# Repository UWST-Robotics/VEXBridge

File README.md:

> ⚠️ **WARNING:** Hey, VEXBridge is still a WIP project. If you run into any bugs or issues, don\'t hesitate to report
> them in the [issues tab](https://github.com/UWST-Robotics/VEXBridge/issues).

<h1 align="center">
VEXBridge
</h1>

<p align="center">
In order to test autonomous routines on mobile robotic systems, receiving feedback during runtime is extremely important. VEXBridge is an app designed to be installed on an SBC such as a Raspberry Pi to relay and present debug data from a serial port (such as a VEX V5 brain) to a developer over Wi-Fi.
</p>

## Features

- 📡 Wireless event log and data communication
- 🗂️ Receive and transmit any data structure
- 🗺️ Display field map for odometry and path planning
- 📈 Graph values over time for easy PID tuning
- ⚠️ Display warnings/errors for both hardware and software diagnostics

## Building

1. Install [Node.js](https://nodejs.org/en) w/ Yarn
2. Install dependencies

```
yarn i
```

3. Run development server

```
yarn run dev
```

## Installing

TODO

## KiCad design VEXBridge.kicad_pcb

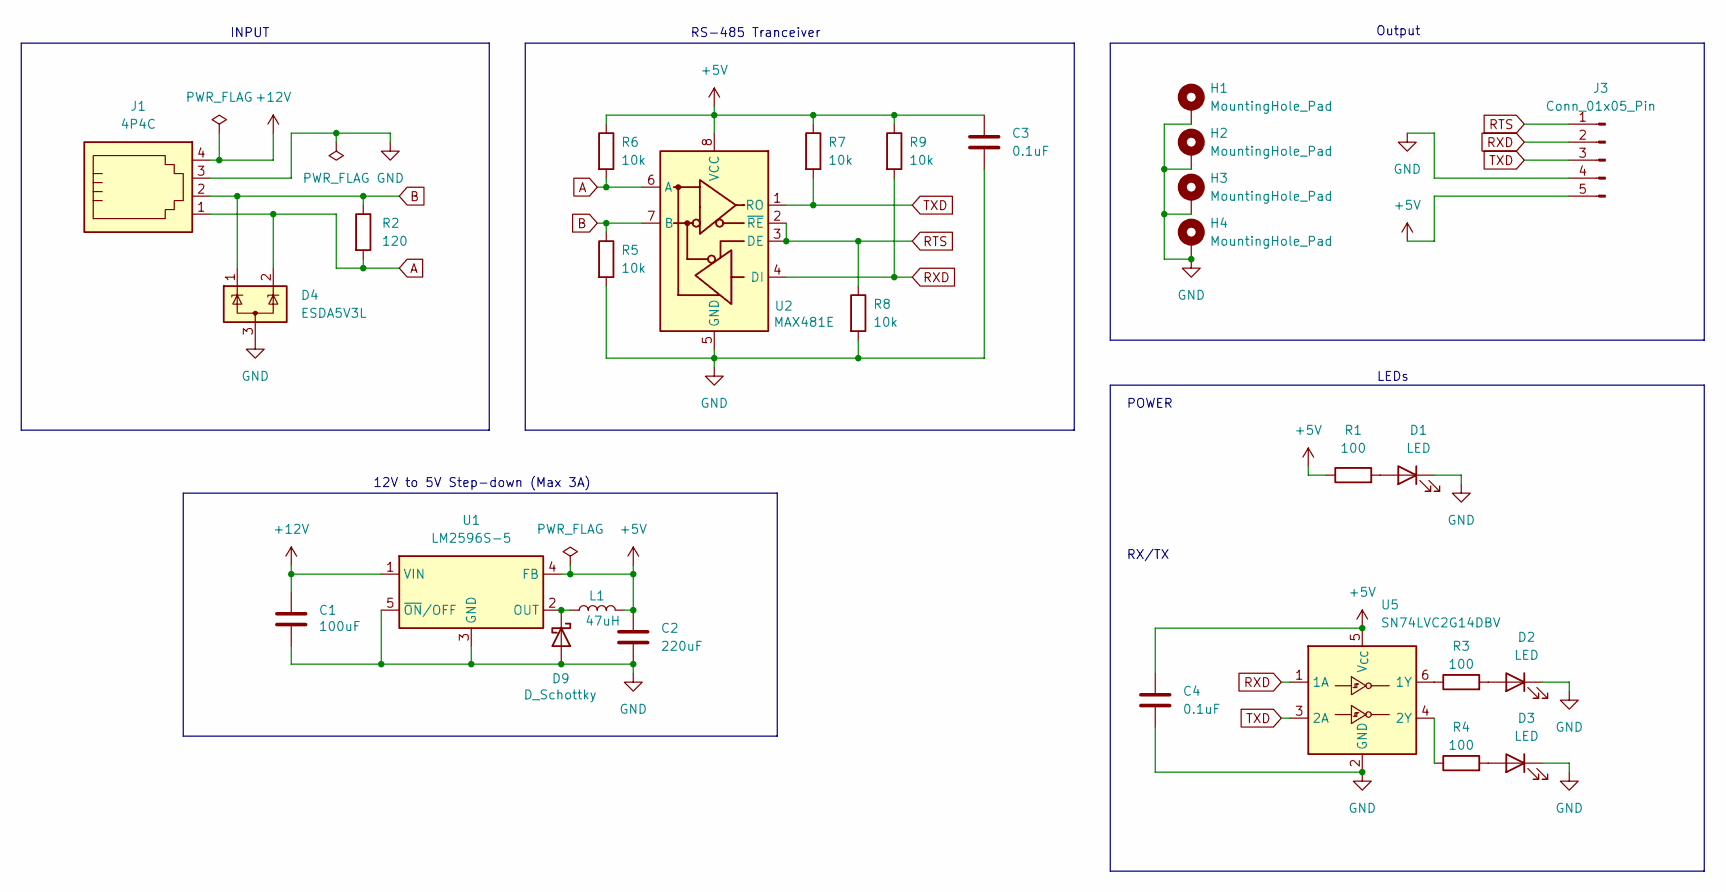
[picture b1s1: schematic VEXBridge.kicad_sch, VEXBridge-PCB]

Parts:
C1: 100uF; CP_Elec_6.3x7.7
C2: 220uF; CP_Elec_6.3x7.7
C3, C4: 0.1uF; C_0402_1005Metric
D1, D2, D3: LED; LED_0603_1608Metric
D4: ESDA5V3L; SOT-23-3
D9: D_Schottky; D_SMA
H1, H2, H3, H4: MountingHole_Pad; MountingHole_2.7mm_M2.5_Pad
J1: 4P4C; RJ9_Evercom_5301-440xxx_Horizontal
J3: Conn_01x05_Pin; PinHeader_1x05_P2.54mm_Vertical
L1: 47uH; L_Coilcraft_LPS4018
R1, R3, R4: 100; R_0805_2012Metric
R2: 120; R_1206_3216Metric
R5, R6, R7, R8, R9: 10k; R_0805_2012Metric
U1: LM2596S-5; TO-263-5_TabPin3
U2: MAX481E; SOIC-8_3.9x4.9mm_P1.27mm
U5: SN74LVC2G14DBV; SOT-23-6

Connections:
+5V: C2.1, C3.1, C4.1, J3.5, L1.2, R1.1, R6.1, R7.1, R9.1, U1.4 (FB), U2.8 (VCC), U5.5 (V_{CC})
+12V: C1.1, J1.4, U1.1 (VIN)
A: D4.2 (K), J1.1, R2.2, R6.2, U2.6 (A)
B: D4.1 (K), J1.2, R2.1, R5.1, U2.7 (B)
GND: C1.2, C2.2, C3.2, C4.2, D1.1 (K), D2.1 (K), D3.1 (K), D4.3 (A), D9.2 (A), H1.1, H2.1, H3.1, H4.1, J1.3, J3.4, R5.2, R8.2, U1.3 (GND), U1.5 (~ON/OFF), U2.5 (GND), U5.2 (GND)
unnamed: D1.2 (A), R1.2
unnamed: D2.2 (A), R3.2
unnamed: D3.2 (A), R4.2
unnamed: D9.1 (K), L1.1, U1.2 (OUT)
unnamed: R3.1, U5.6 (1Y)
unnamed: R4.1, U5.4 (2Y)
RTS: J3.1, R8.1, U2.2 (~RE), U2.3 (DE)
RXD: J3.2, R9.2, U2.4 (DI), U5.1 (1A)
TXD: J3.3, R7.2, U2.1 (RO), U5.3 (2A)

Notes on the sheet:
INPUT
LEDs
RX/TX
POWER
Output
12V to 5V Step-down (Max 3A)
RS-485 Tranceiver

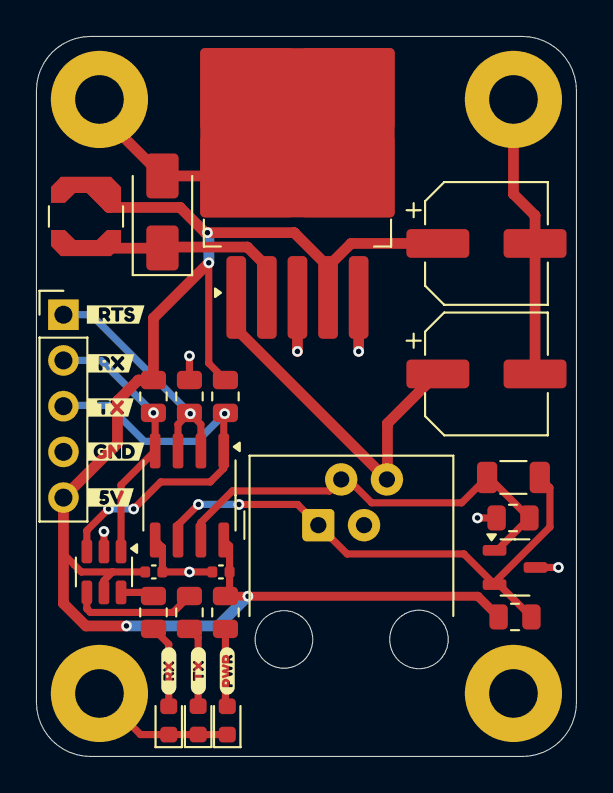
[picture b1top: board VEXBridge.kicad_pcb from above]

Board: 2 copper layers, 30.0 x 40.0 mm, 36 parts (0 on the bottom side), 14 nets.

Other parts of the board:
kibuzzard-675F61D9: G***; kibuzzard-675F61D9
kibuzzard-675F61E2: G***; kibuzzard-675F61E2
kibuzzard-675F61ED: G***; kibuzzard-675F61ED
kibuzzard-675F648F: G***; kibuzzard-675F648F
kibuzzard-675F6148: G***; kibuzzard-675F6148
kibuzzard-675F6473: G***; kibuzzard-675F6473
kibuzzard-675F6495: G***; kibuzzard-675F6495
kibuzzard-676E54E7: G***; kibuzzard-676E54E7

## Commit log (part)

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2024-11-03 Adjustable Max Time Window
2024-11-03 Added Compass Directions
2024-11-04 Added Auto VEX Serial Detection
2024-11-04 Port dev runtime to Electron
2024-11-04 Fixed ESLint
2024-11-05 Added Graph Tab
2024-11-05 Added Multi-select Paths
2024-11-06 Moved Serial Polling out of NT
2024-11-07 Added Remote Polling Services
2024-11-08 Added NonIdealState
2024-11-08 Serial Bug Communication Fixes
2024-11-09 Added Robot State
2024-11-09 Improved Hardware Status Page
2024-11-09 Improve Serial and Terminal parsing
2024-12-10 Bug Fixes
    I genuinely don't remember
2024-12-23 Convert to REST + Socket from Electron
2024-12-24 Fixed Renderer Changed to Work w/ Sockets
2024-12-24 Sync Serial State over Socket/REST
2024-12-25 Added Session Info Sync
2024-12-25 Refactor Server Code
2024-12-26 Removed Cluttered Session System
2024-12-26 Added Charts, Moved Events to Event Service
2024-12-26 Removed server-side value history storage
2024-12-26 Fix Reset Bugs
2024-12-26 Switch to Yarn for CI/CD
2024-12-27 KiCad Files v1
2024-12-27 Added Documentation to README.md
2024-12-27 Fixed README.md Formatting
2024-12-27 Fixed File Names
    Used to be part of the BlueBox project :/
2024-12-27 Modified README.md
2024-12-28 Increased Inductor Footprint
2025-02-02 Added Raw Packet Serialization for RS-485 Support
2025-02-02 Fix GH Actions
2025-02-03 Improved Raw Serial Parsing and Added Additional Packet Types
2025-02-05 Fix Build Pipeline
2025-02-06 Added .deb Bundler
2025-02-08 Fixed .deb Build and Serial Bug Fixes
2025-02-08 Added Batch Updates
2025-02-08 Added deb Build to GH Actions
2025-02-08 Added execute permission to esbuild.cjs
2025-02-08 Add Working Dir to GH Actions Workflow
2025-02-08 Fix File Permission Issues
2025-02-08 8-bit Checksum and Default Serial Port
2025-02-09 Switch from COBS to Flag Byte Stuffing
2025-02-09 Flag Byte Stuffing Bug Fixes
2025-02-09 Bug Fixes
2025-02-09 More Bug Fixes
2025-02-10 Added Winston Logger + Split Value Packet Types
2025-02-10 Added Config File, USB Serial Support, and WIP Settings
2025-02-14 Added "Clear Graph", Fixed Timestamps
2025-02-14 Split AtomFamily into FocusAtom and Parent Atom
2025-03-24 Added Cursor, Settings, and Field Image BG
2025-03-26 Added Arrays, Paths, and Improved Value UI
2025-03-29 Added Settings for Field Map
2025-04-11 Added Value Posting/Fetching
2025-04-14 Write values to serial immediately instead of waiting for Fetch
2025-04-14 Pass Full Value Info in API
2025-05-06 Vision in VexBridge
